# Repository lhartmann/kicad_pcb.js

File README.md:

# kicad_pcb.js
Javascript library for manipulating kicad_pcb files.

License: GPLv3 or newer.

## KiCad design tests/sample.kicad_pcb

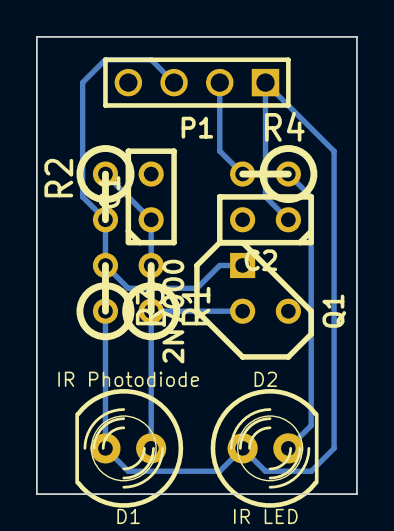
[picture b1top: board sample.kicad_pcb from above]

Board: 2 copper layers, 17.8 x 25.4 mm, 10 parts (0 on the bottom side), 7 nets.

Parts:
C1, C2: 10uF; C1
D1: IR Photodiode; LED-5MM
D2: IR LED; LED-5MM
P1: CONN_4; PIN_ARRAY_4x1
Q1: 2N7000; TO92DGS
R1: 10k; R1
R2, R3: 1k; R1
R4: 150; R1

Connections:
GND: C1.2, C2.2, P1.4, Q1.S
unnamed: C1.1, R1.2, R2.1
unnamed: P1.2, R4.2
unnamed: D2.2, R4.1
unnamed: P1.3, Q1.D, R2.2, R3.2
unnamed: D1.1, Q1.G, R1.1
VCC: C2.1, D1.2, D2.1, P1.1, R3.1

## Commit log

2017-02-10 Initial commit.
2017-02-10 Simplified custom panelisation example.
2017-02-12 Add gr_arc and gr_circle. Add getAllBy*, getFirstBy*.
2017-02-12 Renamed file read/write functions. Renamed sample outputs to out*
